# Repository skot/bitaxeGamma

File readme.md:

```
Open Source is Intrinsic to Bitcoin
```
# The bitaxeGamma
bitaxe is a fully open source Bitcoin ASIC miner aimed at decentralizing mining. bitaxeGamma is the 5th major revision of the bitaxe that now includes the BM1370 ASIC from the Antminer S21 Pro

## Goals
- **Easy**: Just plug it in and mine Bitcoin over WiFi. No external computer needed.
- **Practical**: low cost, low noise, low power, low maintenance. You can run this at home.
- **ASIC Power**: High efficiency and hashrate, based on the latest and greatest Application Specific Integrated Circuits.
- **Versatile**: Mine to any StratumV1 pool, Lottery mine, Solo mine, Or hack it to do whatever you want.
- **Bitcoin Ethos**: Fully open source, permissionless and decentralized to support the worldwide freedom money.

## ASIC
At the heart of the bitaxeGamma is a BM1370 Bitcoin mining ASIC from the Antminer S21 Pro from Bitmain. It's not open source.

- Bitmain claims the BM1370 has 15 J/TH efficiency. We can get pretty close to that with the BitaxeGamma
- The Antminer S21 Pro has a nominal hashrate of 234 TH/s. There are 3 hashboards with 65 chips each, for a total of 195 chips. The bitaxeGamma has a single one of these chips. That means _about_ 1.2 TH/s per bitaxeGamma. Initial testing looks good!
- The BM1370 is brand new and isn't available individually yet. The best place to get these chips is right out of a S21 Pro.
- The BM1370 has a different footprint and pinout from the BM1368, BM1366, BM1397 and BM1387 in previous bitaxe.

## Current Status
- BitaxeGamma 600 is working well and has been released!
- In addition to higher hashrate, the Gamma also uses more power. Please pay attemtion to hash frequency and voltage settings as it's much easier to overheat, especially when using the stock heatsink and fan.
- BM1370 firmware support has been added to [esp-miner](https://github.com/skot/esp-miner)
- Be sure to check the [HW issues](https://github.com/skot/bitaxe/issues) for known bugs, reworks and errata.
- This is an _advanced_ build! You can do it, but if you're not looking for a project, it might be best to buy one pre-assembled from one of the [many sellers](https://bitaxe.org/legit.html). Check [Skot's method](assembly.md) of hand assembling PCBs.

## PCB Hardware
This repo contains all of the design files for the PCB. [KiCAD](https://www.kicad.com) software is used. There is a BOM file for all of the components that get soldered to the PCB. 

- Order PCBs from your favorite PCB shop, like [JLCPCB](https://jlcpcb.com), [SeeedStudio](https://www.seeedstudio.com/fusion_pcb.html), or [PCBWay](https://www.pcbway.com)
    - Gerbers are in the `Manufacturing Files` dir. PCBs are 4-layer, 6mil trace/space and 0.3mm hole compatible. 1oz outer / 0.5oz inner layer thickness works well.
    - Make sure to order stencils too. These are the "paste" layers in the gerbers folder. one for top and one for bottom.
- All PCB parts except the ASIC are available from [DigiKey](https://www.digikey.com/en/products) and others. You can find Digikey part numbers on the DK tab of the BOM

## Extra Hardware
There are a few other hardware components that are needed for a complete bitaxe.

- **Heatsink**
	- [40x40mm heatsink and 5V fan](https://www.aliexpress.com/item/2251832861666365.html) from a random AliExpress seller. The fans are crap, but the heatsinks are good.  
- **Fan**
	- You **must** have active cooling on the bitaxe. The heatsink alone is not enough.
	- The Bitaxe has a connector for a 4pin, 5V PWM fan. 40mm square, 20mm thick fans work nicely with the suggested heatsink. Make sure to get a 5V fan! 12V spin, but slowly overheating your Bitaxe..
	- Upgrade your fan with the [Noctua NF-A4x10](https://noctua.at/en/nf-a4x10-5v-pwm) 5V 4-Pin fan for a much more pleasant experience.
- **Thermal compound**
	- Use a good quality thermal compound between the heatsink and ASIC. [Thermal Grizzly Kryonaut](https://www.amazon.com/Thermal-Grizzly-Kryonaut-Grease-Paste/dp/B011F7W3LU) has been known to work well.  
- **Display**
	- Supports 0.91" SSD1306-based I2C OLED Module. [Example Amazon seller](https://www.amazon.com/gp/product/B08ZY4YBHL). Make sure to get the male pins to interface with the Bitaxe PCB. 
- **Power Supply**
	- **5V DC Only!** Anything else will damage the Bitaxe. Be careful and double-check your power supply is 5V. Many other voltage power supplies use the same connector.
	- The power supply needs to supply in excess of 4A (20W) and not drop below 5V. Often times you have to use a power supply rated for 25-30W to get this!
 		- The [Meanwell GST60A05-P1J](https://www.digikey.com/en/products/detail/mean-well-usa-inc/GST60A05-P1J/7703709) at 30 Watts is the cadillac of 5V PSUs and is working well with the Gamma.  
	- The bitaxe uses a 5.5x2.1mm, center-positive barrel jack. 5.5x2.5mm plugs have been known to work.
- **Stand**
	- The PCB has corner mounting holes. You're going to want a stand to mount your Bitaxe. Many excellent 3D printed designs are available.

## Firmware
- The [ESP-Miner](https://github.com/skot/ESP-Miner) has initial support for the BM1370 ASIC. Improvements are ongoing.

### ESP32 Programming Requirements
- As of the bitaxeUltra, all ESP32 programming is done through a USB-C cable and connector on the bitaxe. See [ESP-Miner](https://github.com/skot/ESP-Miner) for more details.

## More Information
- Project page at [bitaxe.org](https://bitaxe.org)
- [Open Source Miners United](discord.gg/osmu) Discord chat
- [building.md](building.md) for PCB ordering tips
- [assembly.md](assembly.md) for assembly tips

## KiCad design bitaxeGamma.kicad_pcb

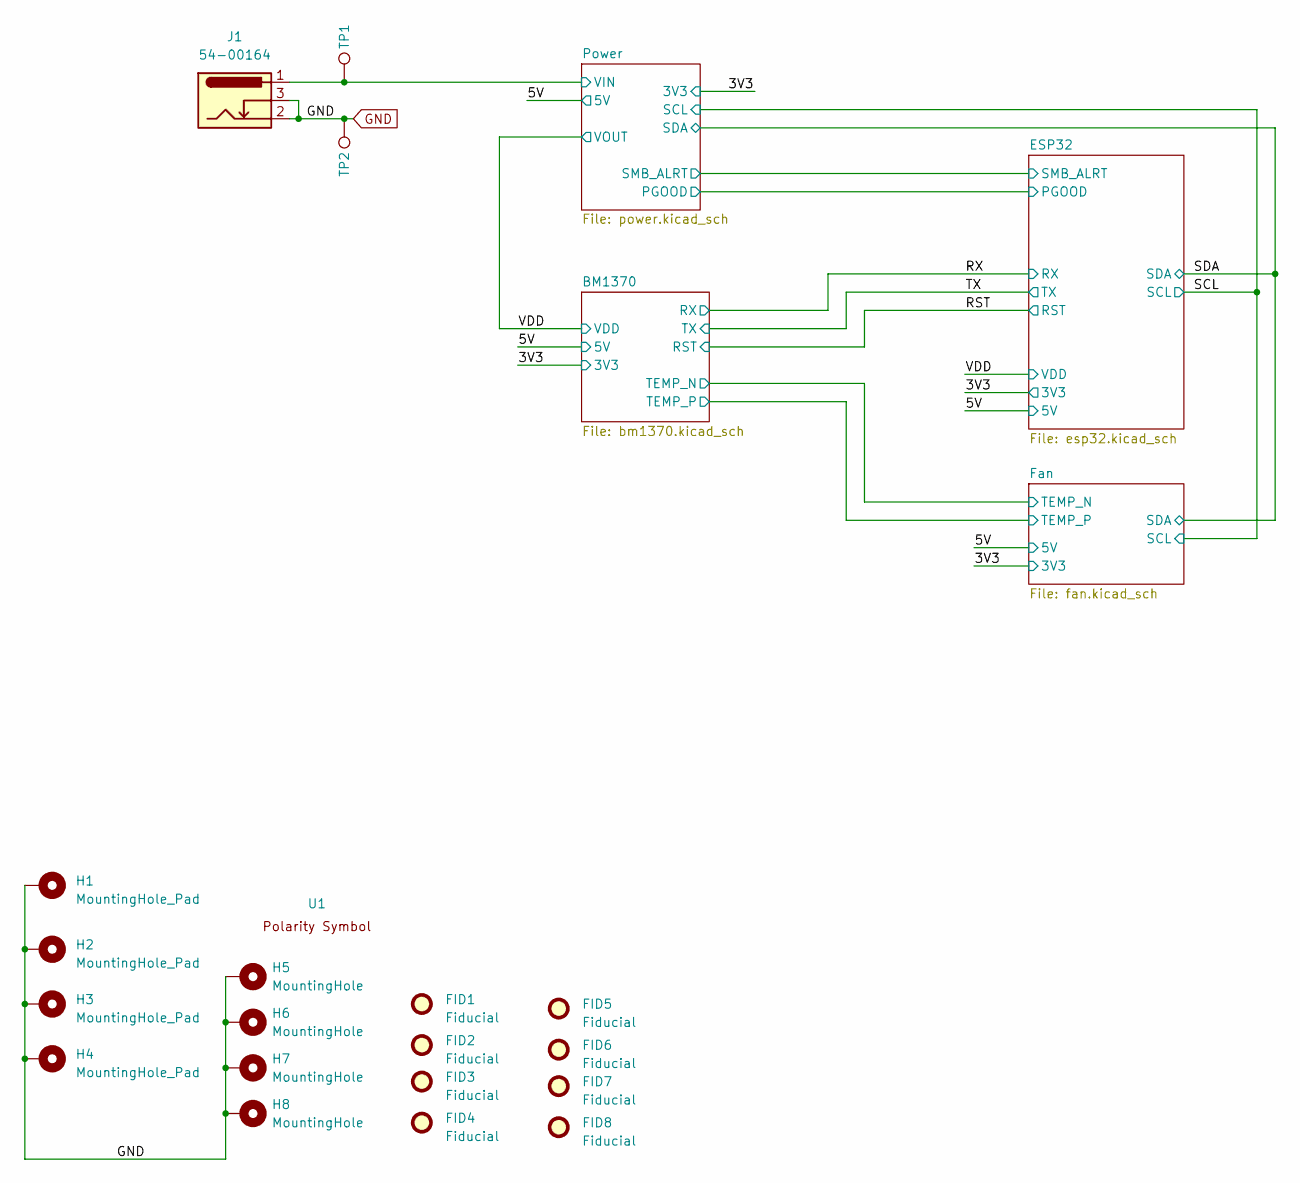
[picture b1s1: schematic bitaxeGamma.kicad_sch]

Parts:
FID1, FID2, FID3, FID4, FID5, FID6, FID7, FID8: Fiducial; Fiducial_1mm_Mask2mm
H1, H2, H3, H4: MountingHole_Pad; MountingHole_3mm_Pad_Via
H5, H6, H7, H8: MountingHole; MountingHole_3.2mm_M3_Pad
J1: 54-00164; TENSILITY_54-00164; PARTNO 54-00164; LCSC C431534
TP1, TP2: TestPoint; TestPoint_Pad_D1.5mm
U1: polarity

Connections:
/5V: J1.1, TP1.1; also elsewhere on the board

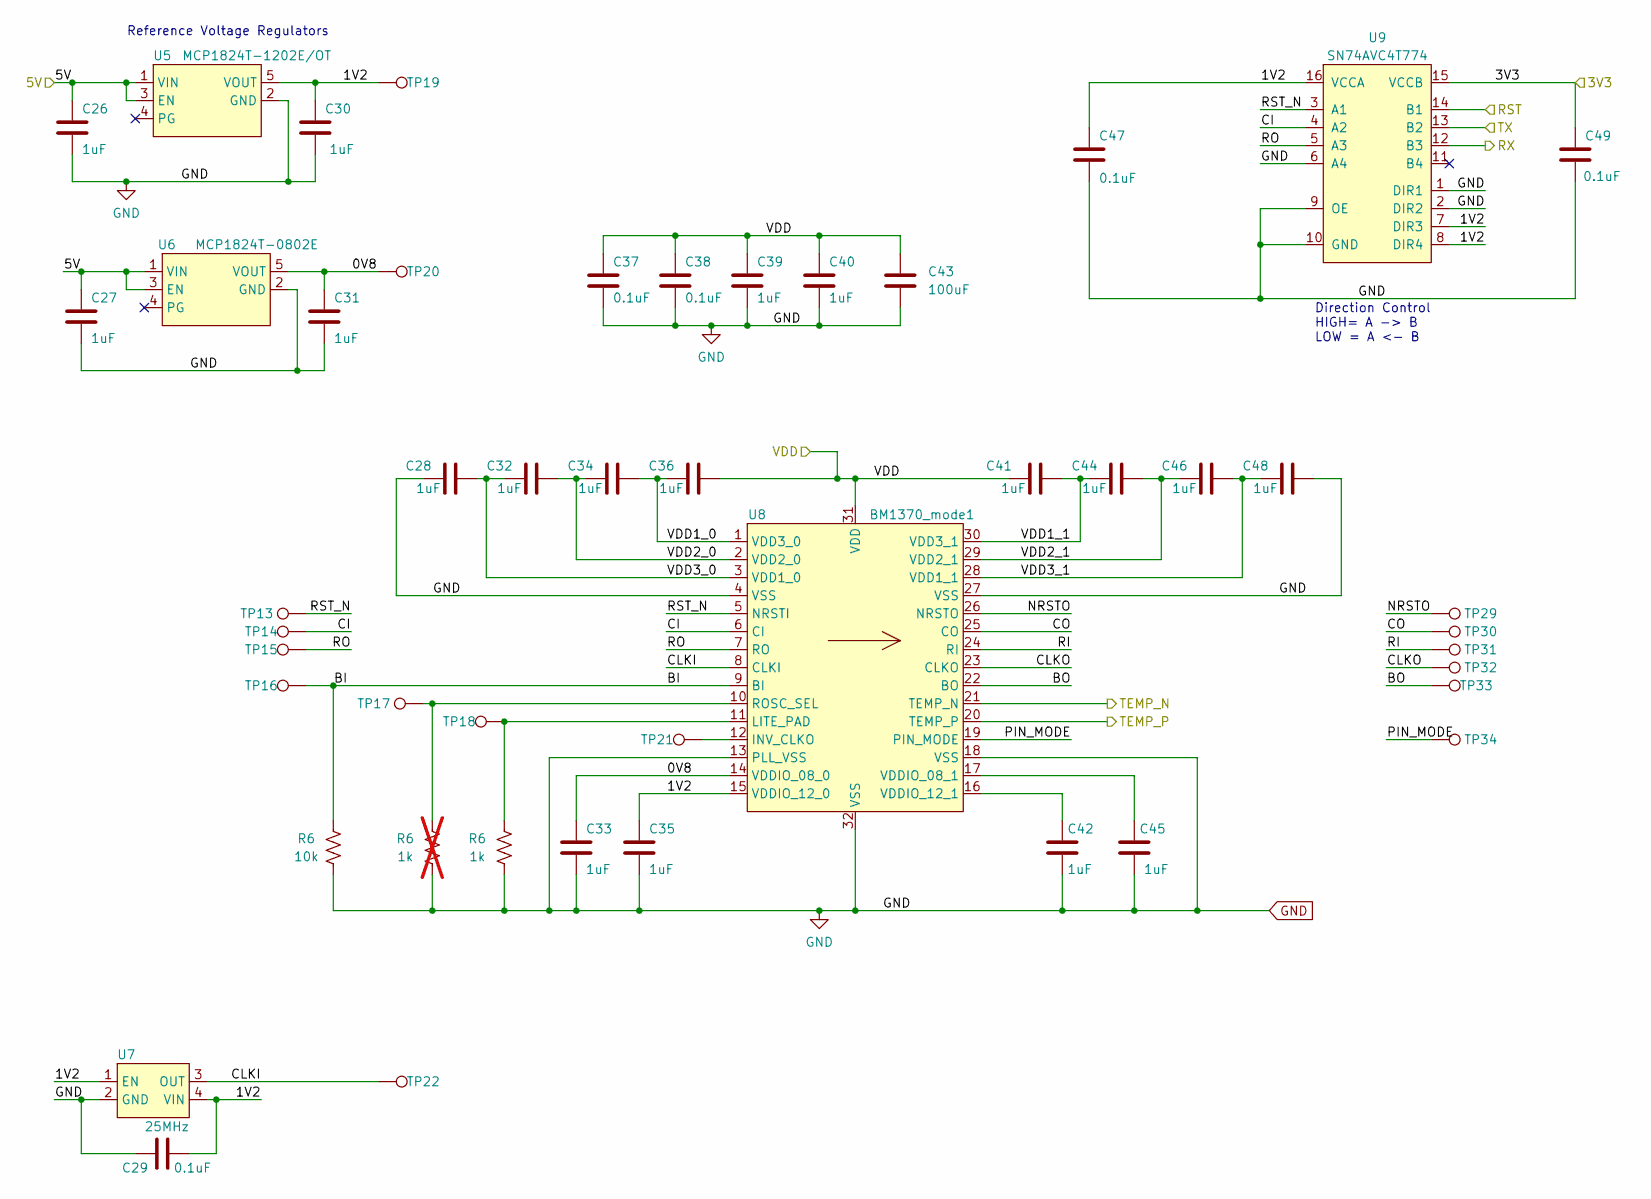
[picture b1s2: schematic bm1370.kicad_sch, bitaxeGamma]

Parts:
C26, C27, C28, C30, C31, C32, C33, C34, C35, C36, C39, C40, C41, C42, C44, C45, C46, C48: 1uF; C_0402_1005Metric; PARTNO EMK105BJ105MV-F
C29, C37, C38, C47, C49: 0.1uF; C_0402_1005Metric; PARTNO CL05A104KO5NNNC
C43: 100uF; C_1206_3216Metric; PARTNO CL31A107MQHNNNE
R6: 1k; R_0402_1005Metric; PARTNO RC0402FR-071KL; not fitted
TP13, TP14, TP15, TP16, TP17, TP18, TP19, TP20, TP21, TP22, TP29, TP30, TP31, TP32, TP33, TP34: TestPoint; TestPoint_Pad_D1.5mm
U5: MCP1824T-1202E/OT; SOT-23-5; PARTNO MCP1824T-1202E/OT
U6: MCP1824T-0802E; SOT-23-5; PARTNO MCP1824T-0802E/OT
U7: 25MHz; SMD3225-4P; PARTNO SX3M25.000E20F30THN; LCSC C5137262
U8: BM1370_mode1; BM1370
U9: SN74AVC4T774; TSSOP-16_4.4x5mm_P0.65mm; PARTNO SN74AVC4T774PWR

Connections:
/3V3: C49.1, U9.15 (VCCB); also elsewhere on the board
/5V: C26.1, C27.1, U5.1 (VIN), U5.3 (EN), U6.1 (VIN), U6.3 (EN); also elsewhere on the board
/BM1370/0V8: C31.1, C33.1, TP20.1, U6.5 (VOUT), U8.14 (VDDIO_08_0)
/BM1370/1V2: C29.2, C30.1, C35.1, C47.1, TP19.1, U5.5 (VOUT), U7.1 (EN), U7.4 (VIN), U8.15 (VDDIO_12_0), U9.7 (DIR3), U9.8 (DIR4), U9.16 (VCCA)
/BM1370/BO: TP33.1, U8.22 (BO)
/BM1370/CI: TP14.1, U8.6 (CI), U9.4 (A2)
/BM1370/CLKI: TP22.1, U7.3 (OUT), U8.8 (CLKI)
/BM1370/CLKO: TP32.1, U8.23 (CLKO)
/BM1370/CO: TP30.1, U8.25 (CO)
/BM1370/NRSTO: TP29.1, U8.26 (NRSTO)
/BM1370/PIN_MODE: TP34.1, U8.19 (PIN_MODE)
/BM1370/RI: TP31.1, U8.24 (RI)
/BM1370/RO: TP15.1, U8.7 (RO), U9.5 (A3)
/BM1370/RST_N: TP13.1, U8.5 (NRSTI), U9.3 (A1)
/BM1370/VDD1_0: C34.2, C36.1, U8.1 (VDD3_0)
/BM1370/VDD1_1: C41.2, C44.1, U8.30 (VDD3_1)
/BM1370/VDD2_0: C32.2, C34.1, U8.2 (VDD2_0)
/BM1370/VDD2_1: C44.2, C46.1, U8.29 (VDD2_1)
/BM1370/VDD3_0: C28.2, C32.1, U8.3 (VDD1_0)
/BM1370/VDD3_1: C46.2, C48.1, U8.28 (VDD1_1)
/Fan/TEMP_N: U8.21 (TEMP_N); also elsewhere on the board
/Fan/TEMP_P: U8.20 (TEMP_P); also elsewhere on the board
/RST: U9.14 (B1); also elsewhere on the board
/RX: U9.12 (B3); also elsewhere on the board
/TX: U9.13 (B2); also elsewhere on the board
/VDD: C36.2, C37.1, C38.1, C39.1, C40.1, C41.1, C43.1, U8.31 (VDD); also elsewhere on the board
unnamed: TP21.1, U8.12 (INV_CLKO)
unnamed: C45.1, U8.17 (VDDIO_08_1)
unnamed: C42.1, U8.16 (VDDIO_12_1)

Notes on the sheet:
Reference Voltage Regulators
Direction Control HIGH= A -> B LOW = A <- B

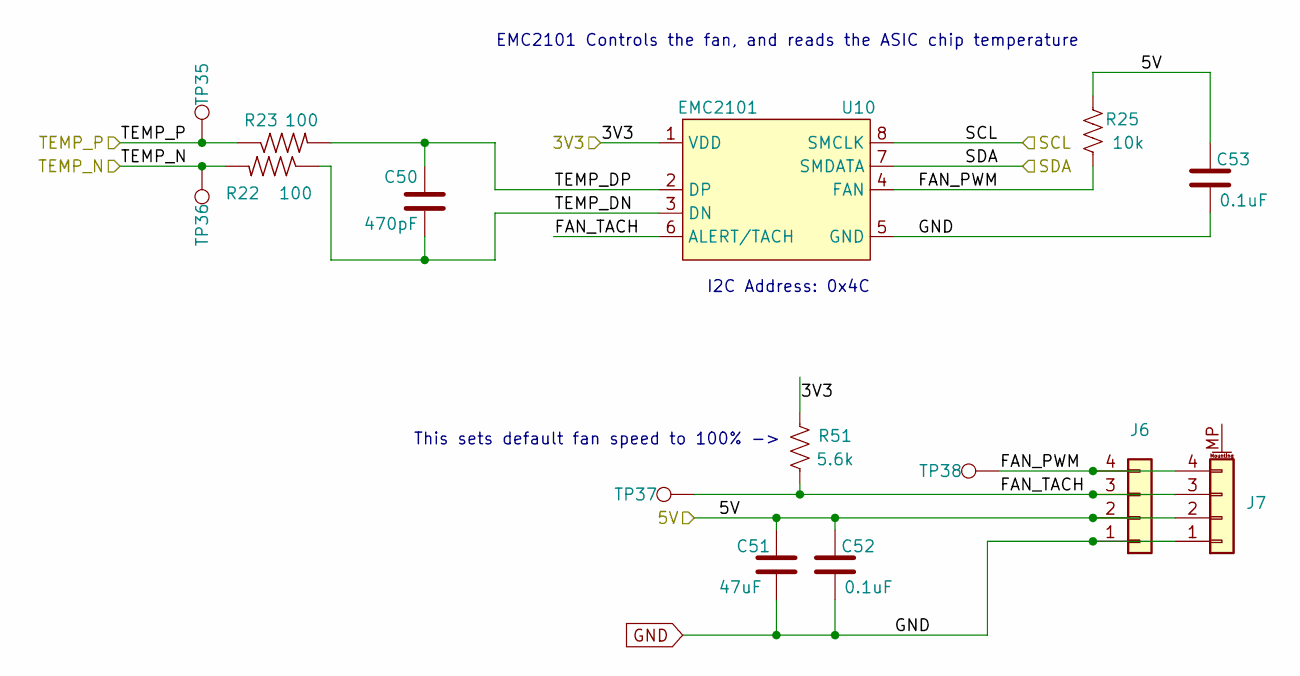
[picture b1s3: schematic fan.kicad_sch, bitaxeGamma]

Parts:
C50: 470pF; C_0402_1005Metric; PARTNO CL05B471KB5NNNC
C51: 47uF; C_1210_3225Metric; PARTNO CL32A476KOJNNNE
C52, C53: 0.1uF; C_0402_1005Metric; PARTNO CL05A104KO5NNNC
J6: Conn_01x04; 470531000; PARTNO 0470531000
J7: Conn_01x04; JST_SH_BM04B-SRSS-TB_1x04-1MP_P1.00mm_Vertical
R22, R23: 100; R_0402_1005Metric; PARTNO RC0402FR-07100RL
R25: 10k; R_0402_1005Metric; PARTNO RC0402JR-0710KL
R51: 5.6k; R_0402_1005Metric; PARTNO RC0402FR-135K6L
TP35, TP36, TP37, TP38: TestPoint; TestPoint_Pad_D1.5mm
U10: EMC2101; TSSOP-8_3x3mm_P0.65mm; PARTNO EMC2101-R-ACZL-TR

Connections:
/3V3: U10.1 (VDD); also elsewhere on the board
/5V: C51.1, C52.1, C53.1, J6.2, J7.2, R25.2; also elsewhere on the board
/Fan/FAN_PWM: J6.4, J7.4, R25.1, TP38.1, U10.4 (FAN)
/Fan/FAN_TACH: J6.3, J7.3, TP37.1, U10.6 (ALERT/TACH); also elsewhere on the board
/Fan/TEMP_DN: C50.2, R22.1, U10.3 (DN)
/Fan/TEMP_DP: C50.1, R23.2, U10.2 (DP)
/Fan/TEMP_N: R22.2, TP36.1; also elsewhere on the board
/Fan/TEMP_P: R23.1, TP35.1; also elsewhere on the board
/SCL: U10.8 (SMCLK); also elsewhere on the board
/SDA: U10.7 (SMDATA); also elsewhere on the board

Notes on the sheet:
EMC2101 Controls the fan, and reads the ASIC chip temperature
This sets default fan speed to 100% ->
I2C Address: 0x4C

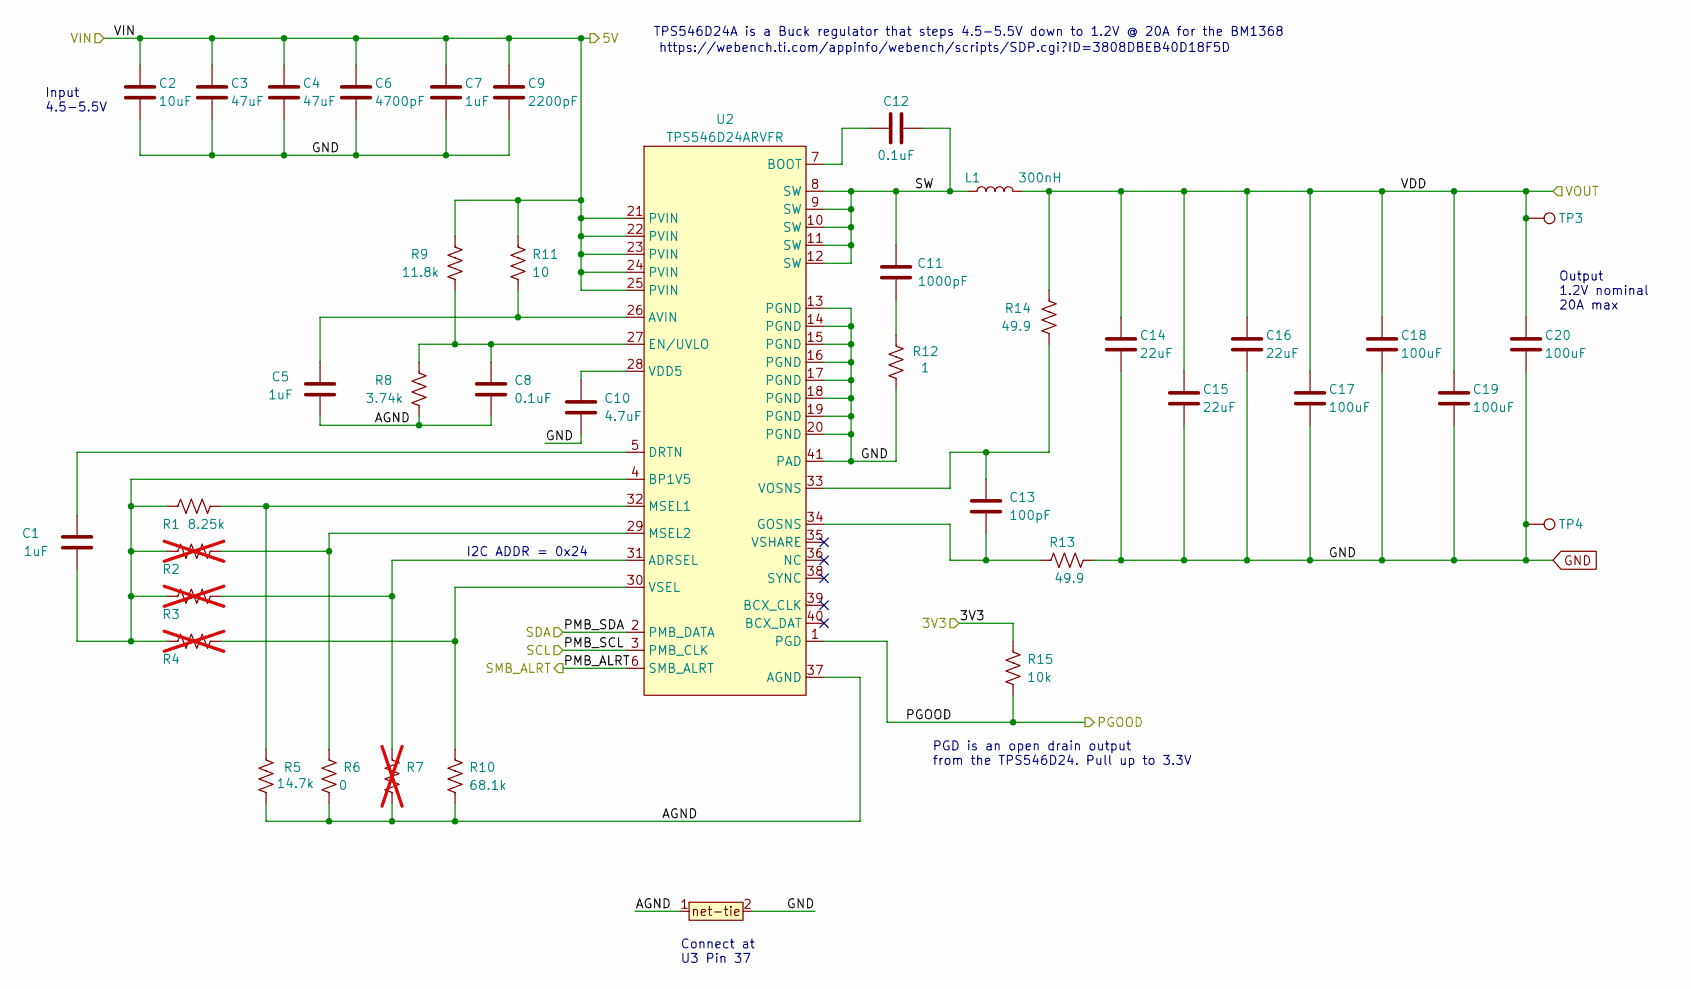
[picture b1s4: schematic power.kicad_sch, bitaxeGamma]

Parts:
C1, C5, C7: 1uF; C_0402_1005Metric; PARTNO EMK105BJ105MV-F
C2: 10uF; C_0805_2012Metric; PARTNO CL21A106KOQNNNE
C3, C4: 47uF; C_1210_3225Metric; PARTNO CL32A476KOJNNNE
C6: 4700pF; C_0402_1005Metric; PARTNO GRM155R71E472KA01D
C8, C12: 0.1uF; C_0402_1005Metric; PARTNO CL05A104KO5NNNC
C9: 2200pF; C_0402_1005Metric; PARTNO GRM155R61H222KA01D
C10: 4.7uF; C_0402_1005Metric; PARTNO GRM155R61A475MEAAD
C11: 1000pF; C_0805_2012Metric; PARTNO CC0805KRX7R9BB102
C13: 100pF; C_0402_1005Metric; PARTNO 885012005013
C14, C15, C16: 22uF; C_0805_2012Metric; PARTNO GRM21BR61A226ME44L
C17, C18, C19, C20: 100uF; C_1206_3216Metric; PARTNO CL31A107MQHNNNE
L1: 300nH; SLC1175-271MEC_COC; PARTNO SLC1175-301MEC; Mouser 994-SLC1175-271MEC
R1: 8.25k; R_0402_1005Metric; PARTNO RC0402FR-078K25L
R2, R3, R4, R7: R_0402_1005Metric; not fitted
R5: 14.7k; R_0402_1005Metric; PARTNO RC0402FR-0714K7L
R6: 0; R_0402_1005Metric; PARTNO RC0402JR-070RL
R8: 3.74k; R_0402_1005Metric; PARTNO RC0402FR-073K74L
R9: 11.8k; R_0402_1005Metric; PARTNO RC0402FR-0711K8L
R10: 68.1k; R_0402_1005Metric; PARTNO RC0402FR-0768K1L
R11: 10; R_0402_1005Metric; PARTNO RC0402FR-0710RL
R12: 1; R_1206_3216Metric; PARTNO CSR1206FT1R00
R13, R14: 49.9; R_0402_1005Metric; PARTNO RC0402FR-0749R9L
R15: 10k; R_0402_1005Metric; PARTNO RC0402JR-0710KL
T1: net-tie; NetTie-0.25mm; PARTNO 2R5TPE220MAFB
TP3, TP4: TestPoint; TestPoint_Pad_D1.5mm
U2: TPS546D24ARVFR; LQFN40-CLIP; PARTNO TPS546D24ARVFR

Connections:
/3V3: R15.2; also elsewhere on the board
/5V: C2.1, C3.1, C4.1, C6.1, C7.1, C9.1, R9.1, R11.1, U2.21 (PVIN), U2.22 (PVIN), U2.23 (PVIN), U2.24 (PVIN), U2.25 (PVIN); also elsewhere on the board
/Power/PGOOD: R15.1, U2.1 (PGD); also elsewhere on the board
/Power/PMB_ALRT: U2.6 (SMB_ALRT); also elsewhere on the board
/Power/SW: C11.2, C12.2, L1.1, U2.8 (SW), U2.9 (SW), U2.10 (SW), U2.11 (SW), U2.12 (SW)
/SCL: U2.3 (PMB_CLK); also elsewhere on the board
/SDA: U2.2 (PMB_DATA); also elsewhere on the board
/VDD: C14.1, C15.1, C16.1, C17.1, C18.1, C19.1, C20.1, L1.2, R14.1, TP3.1; also elsewhere on the board
unnamed: C11.1, R12.2
unnamed: R3.2, R7.1, U2.31 (ADRSEL)
unnamed: C5.2, R11.2, U2.26 (AVIN)
unnamed: C12.1, U2.7 (BOOT)
unnamed: C1.2, R1.1, R2.1, R3.1, R4.1, U2.4 (BP1V5)
unnamed: C1.1, U2.5 (DRTN)
unnamed: C8.1, R8.1, R9.2, U2.27 (EN/UVLO)
unnamed: C13.2, R13.1, U2.34 (GOSNS)
unnamed: R1.2, R5.2, U2.32 (MSEL1)
unnamed: C10.1, U2.28 (VDD5)
unnamed: C13.1, R14.2, U2.33 (VOSNS)
unnamed: R4.2, R10.1, U2.30 (VSEL)

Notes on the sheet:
TPS546D24A is a Buck regulator that steps 4.5-5.5V down to 1.2V @ 20A for the BM1368
https://webench.ti.com/appinfo/webench/scripts/SDP.cgi?ID=3808DBEB40D18F5D
Input 4.5-5.5V
PGD is an open drain output from the TPS546D24. Pull up to 3.3V
I2C ADDR = 0x24
Output 1.2V nominal 20A max
Connect at U3 Pin 37

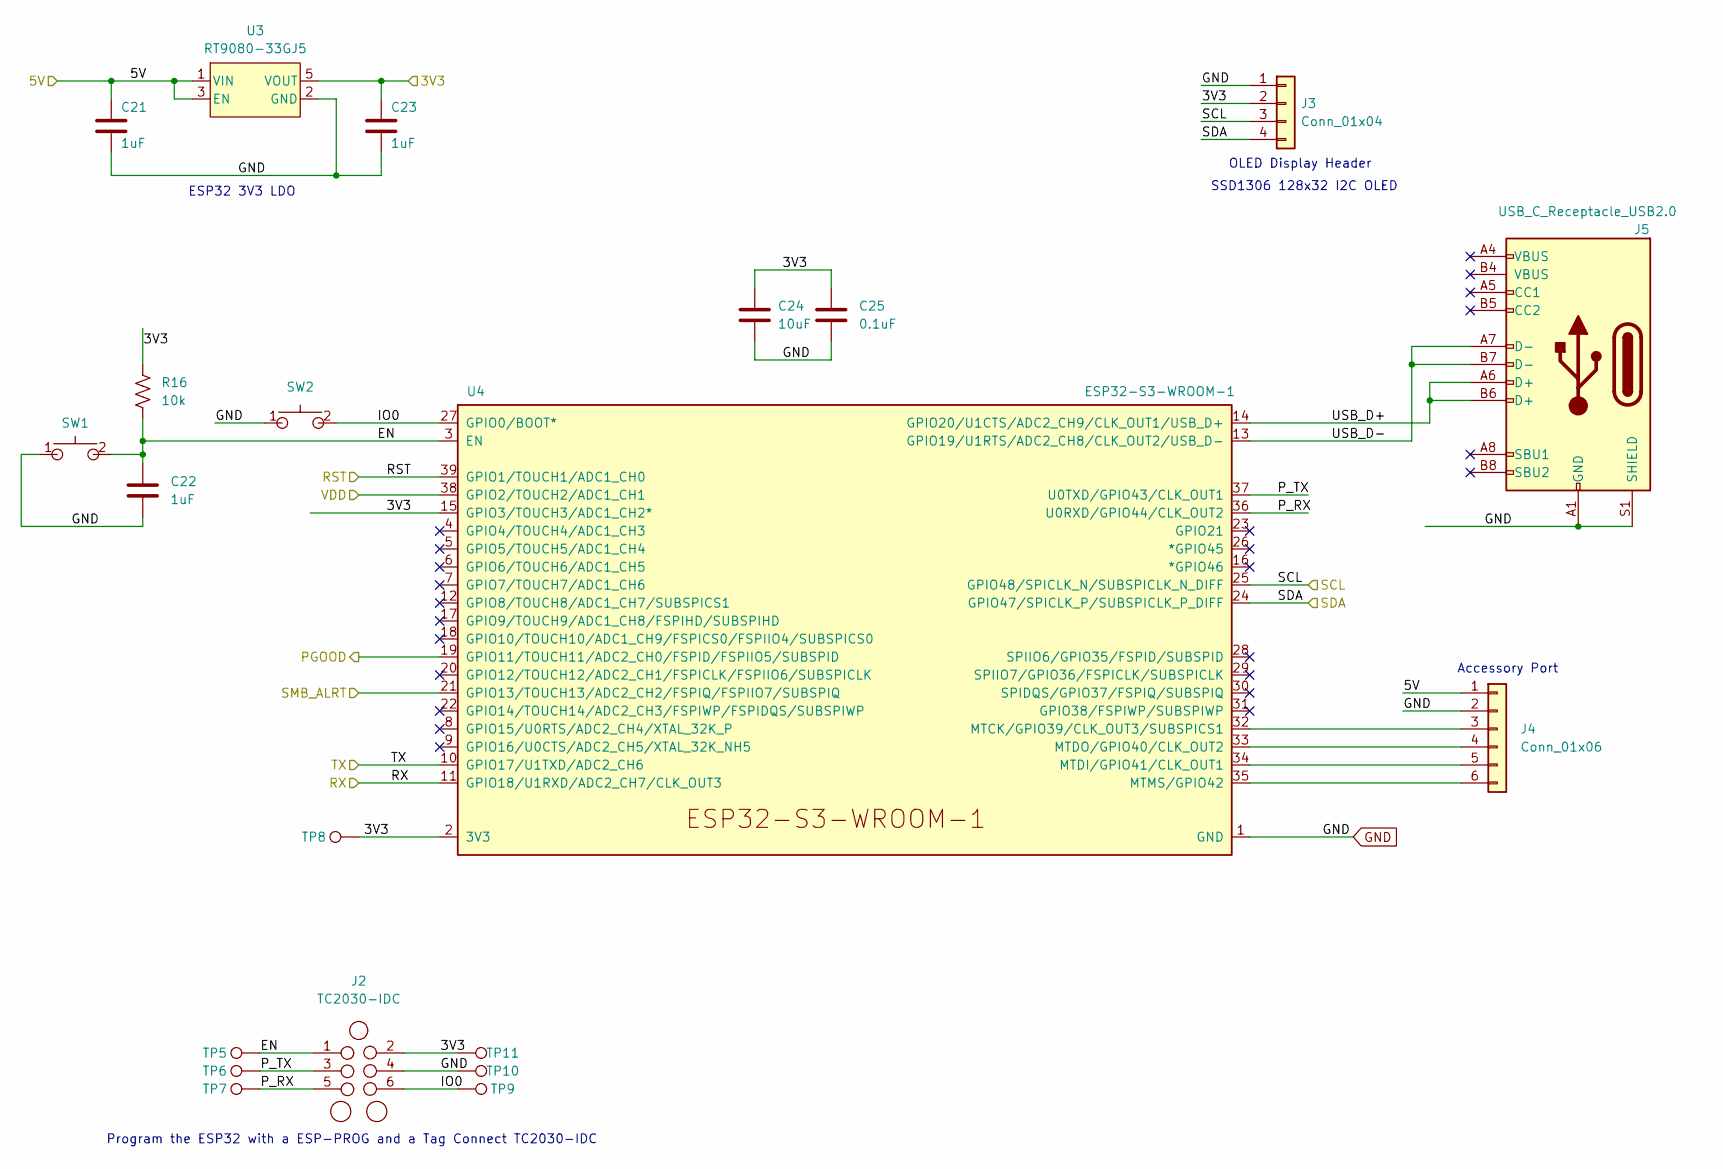
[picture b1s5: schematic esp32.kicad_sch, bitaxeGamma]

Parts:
C21, C22, C23: 1uF; C_0402_1005Metric; PARTNO EMK105BJ105MV-F
C24: 10uF; C_0805_2012Metric; PARTNO CL21A106KOQNNNE
C25: 0.1uF; C_0402_1005Metric; PARTNO CL05A104KO5NNNC
J2: TC2030-IDC; Tag-Connect_TC2030-IDC-NL_2x03_P1.27mm_Vertical
J3: Conn_01x04; PinHeader_1x04_P2.54mm_Vertical_shifted; PARTNO NPTC041KFXC-RC
J4: Conn_01x06; PinHeader_1x06_P2.54mm_Vertical
J5: USB_C_Receptacle_USB2.0; USB_C_Receptacle_GCT_USB4105-xx-A; PARTNO USB4105-GF-A
R16: 10k; R_0402_1005Metric; PARTNO RC0402JR-0710KL
SW1, SW2: GT-TC029B-H025-L1N; SW_CS1213AGF260_CRS; PARTNO CS1213AGF260
TP5, TP6, TP7, TP8, TP9, TP10, TP11: TestPoint; TestPoint_Pad_D1.5mm
U3: RT9080-33GJ5; PARTNO RT9080-33GJ5
U4: ESP32-S3-WROOM-1; PARTNO ESP32-S3-WROOM-1-N16R8

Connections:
/3V3: C23.1, C24.1, C25.1, J2.2, J3.2, R16.1, TP8.1, TP11.1, U3.5 (VOUT), U4.2 (3V3), U4.15 (GPIO3/TOUCH3/ADC1_CH2*); also elsewhere on the board
/5V: C21.1, J4.1, U3.1 (VIN), U3.3 (EN); also elsewhere on the board
/ESP32/EN: C22.1, J2.1, R16.2, SW1.2, TP5.1, U4.3 (EN)
/ESP32/IO0: J2.6, SW2.2, TP9.1, U4.27 (GPIO0/BOOT*)
/ESP32/P_RX: J2.5, TP7.1, U4.36 (U0RXD/GPIO44/CLK_OUT2)
/ESP32/P_TX: J2.3, TP6.1, U4.37 (U0TXD/GPIO43/CLK_OUT1)
/ESP32/USB_D+: J5.A6 (D+), J5.B6 (D+), U4.14 (GPIO20/U1CTS/ADC2_CH9/CLK_OUT1/USB_D+)
/ESP32/USB_D-: J5.A7 (D-), J5.B7 (D-), U4.13 (GPIO19/U1RTS/ADC2_CH8/CLK_OUT2/USB_D-)
/Power/PGOOD: U4.19 (GPIO11/TOUCH11/ADC2_CH0/FSPID/FSPIIO5/S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); also elsewhere on the board
/Power/PMB_ALRT: U4.21 (GPIO13/TOUCH13/ADC2_CH2/FSPIQ/FSPIIO7/S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); also elsewhere on the board
/RST: U4.39 (GPIO1/TOUCH1/ADC1_CH0); also elsewhere on the board
/RX: U4.11 (GPIO18/U1RXD/ADC2_CH7/CLK_OUT3); also elsewhere on the board
/SCL: J3.3, U4.25 (GPIO48/SPICLK_N/SUBSPICLK_N_DIFF); also elsewhere on the board
/SDA: J3.4, U4.24 (GPIO47/SPICLK_P/SUBSPICLK_P_DIFF); also elsewhere on the board
/TX: U4.10 (GPIO17/U1TXD/ADC2_CH6); also elsewhere on the board
/VDD: U4.38 (GPIO2/TOUCH2/ADC1_CH1); also elsewhere on the board
unnamed: J4.3, U4.32 (MTCK/GPIO39/CLK_OUT3/SUBSPICS1)
unnamed: J4.4, U4.33 (MTDO/GPIO40/CLK_OUT2)
unnamed: J4.5, U4.34 (MTDI/GPIO41/CLK_OUT1)
unnamed: J4.6, U4.35 (MTMS/GPIO42)

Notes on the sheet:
Accessory Port
ESP32 3V3 LDO
Program the ESP32 with a ESP-PROG and a Tag Connect TC2030-IDC
SSD1306 128x32 I2C OLED
OLED Display Header

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
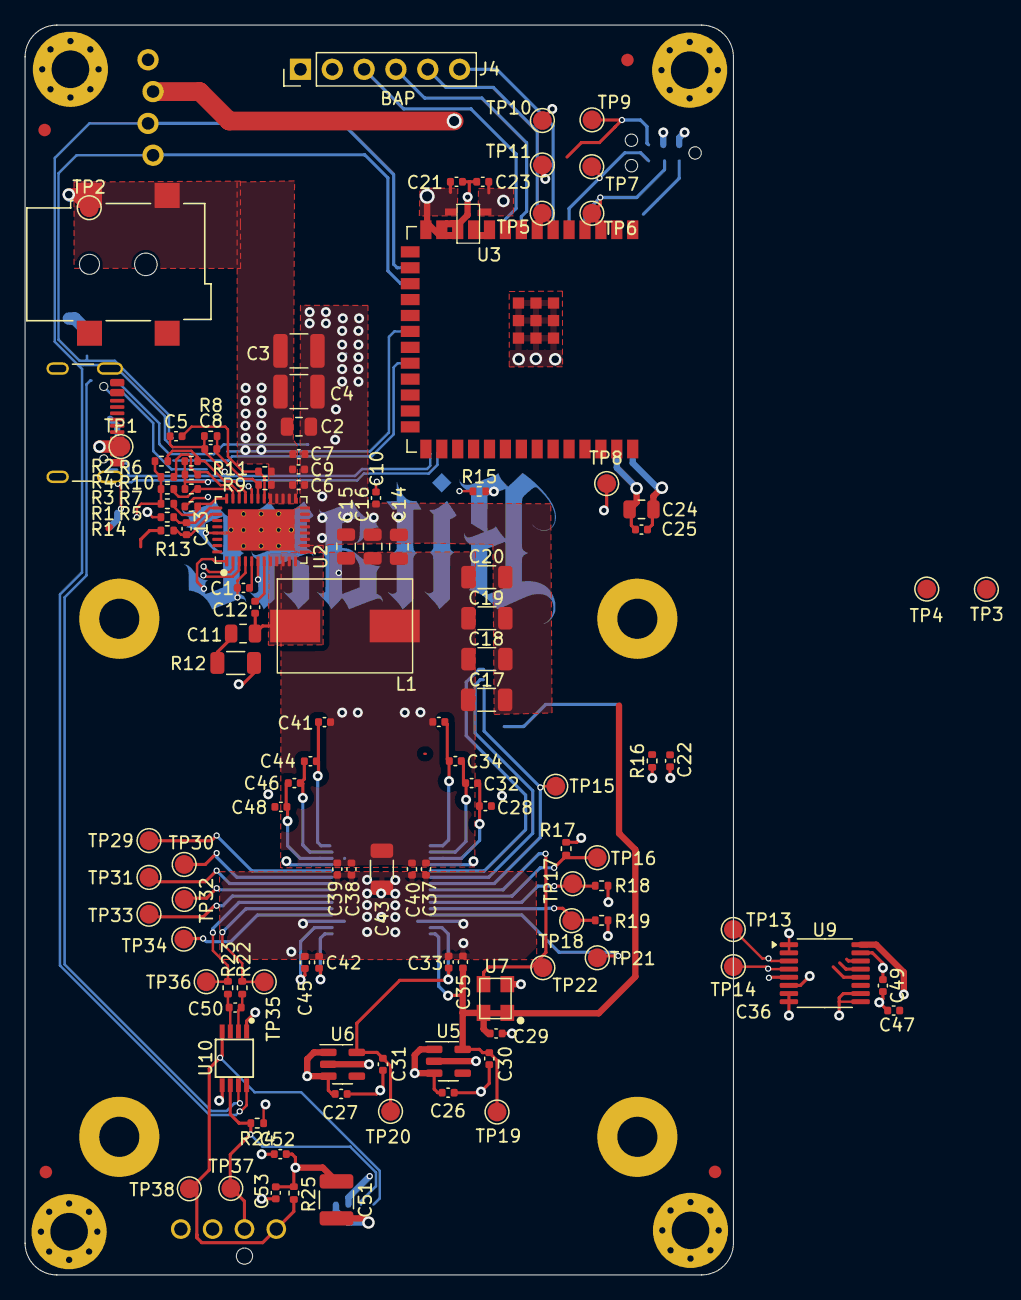
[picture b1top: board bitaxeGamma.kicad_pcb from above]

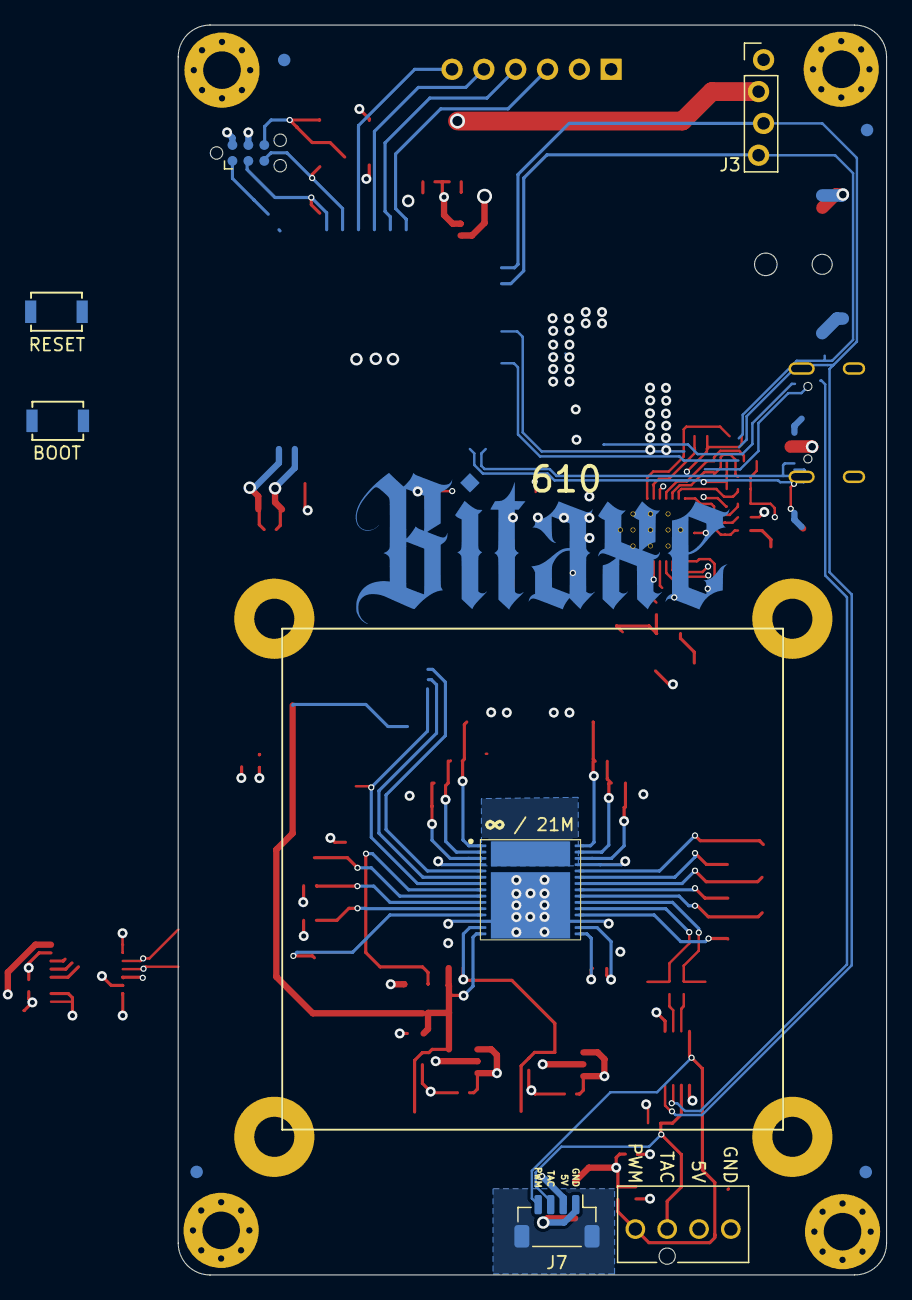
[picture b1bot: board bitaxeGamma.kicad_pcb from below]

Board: 4 copper layers, 56.5 x 99.8 mm, 144 parts (12 on the bottom side), 66 nets.

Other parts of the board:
R17: 10k; R_0402_1005Metric
R18, R19: 1k; R_0402_1005Metric
R24: 5.6k; R_0402_1005Metric

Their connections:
/3V3: R24.2; also elsewhere on the board
/Fan/FAN_TACH: R24.1; also elsewhere on the board

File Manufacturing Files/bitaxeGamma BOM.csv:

Qty,Reference,Value,Footprint,DK,PARTNO,DNP
1,C6,4700pF,Capacitor_SMD:C_0402_1005Metric,490-1309-1-ND,GRM155R71E472KA01D,
1,C9,2200pF,Capacitor_SMD:C_0402_1005Metric,490-8257-1-ND,GRM155R61H222KA01D,
1,C10,4.7uF,Capacitor_SMD:C_0402_1005Metric,490-14306-1-ND,GRM155R61A475MEAAD,
1,C11,1000pF,Capacitor_SMD:C_0805_2012Metric,311-1127-1-ND,CC0805KRX7R9BB102,
1,C13,100pF,Capacitor_SMD:C_0402_1005Metric,732-7431-1-ND,8.85012E+11,
1,C50,470pF,Capacitor_SMD:C_0402_1005Metric,1276-1566-1-ND,CL05B471KB5NNNC,
24,C1 C5 C7 C21 C22 C23 C26 C27 C28 C30 C31 C32 C33 C34 C35 C36 C39 C40 C41 C42 C44 C45 C46 C48,1uF,Capacitor_SMD:C_0402_1005Metric,587-5514-1-ND,EMK105BJ105MV-F,
3,C14 C15 C16,22uF,Capacitor_SMD:C_0805_2012Metric,490-10746-1-ND,GRM21BR61A226ME44L,
5,C17 C18 C19 C20 C43,100uF,Capacitor_SMD:C_1206_3216Metric,1276-1782-1-ND,CL31A107MQHNNNE,
2,C2 C24,10uF,Capacitor_SMD:C_0805_2012Metric,1276-1096-1-ND,CL21A106KOQNNNE,
3,C3 C4 C51,47uF,Capacitor_SMD:C_1210_3225Metric,1276-3376-1-ND,CL32A476KOJNNNE,
10,C8 C12 C25 C29 C37 C38 C47 C49 C52 C53,0.1uF,Capacitor_SMD:C_0402_1005Metric,1276-1234-1-ND,CL05A104KO5NNNC,
1,J1,54-00164,bitaxe:TENSILITY_54-00164,839-54-00164CT-ND,54-00164,
1,J5,USB_C_Receptacle_USB2.0,bitaxe:USB_C_Receptacle_GCT_USB4105-xx-A,2073-USB4105-GF-ACT-ND,USB4105-GF-A,
1,J6,Conn_01x04,bitaxe:470531000,WM4330-ND,470531000,
1,L1,300nH,bitaxe:SLC1175-271MEC_COC,,SLC1175-301MEC,
1,R1,8.25k,Resistor_SMD:R_0402_1005Metric,311-8.25KLRCT-ND,RC0402FR-078K25L,
1,R5,14.7k,Resistor_SMD:R_0402_1005Metric,YAG2984CT-ND,RC0402FR-0714K7L,
1,R6,0,Resistor_SMD:R_0402_1005Metric,311-0.0JRCT-ND,RC0402JR-070RL,
1,R8,3.74k,Resistor_SMD:R_0402_1005Metric,311-3.74KLRCT-ND,RC0402FR-073K74L,
1,R9,11.8k,Resistor_SMD:R_0402_1005Metric,YAG2958CT-ND,RC0402FR-0711K8L,
1,R10,68.1k,Resistor_SMD:R_0402_1005Metric,YAG3213CT-ND,RC0402FR-0768K1L,
1,R11,10,Resistor_SMD:R_0402_1005Metric,311-10.0LRCT-ND,RC0402FR-0710RL,
1,R12,1,Resistor_SMD:R_1206_3216Metric,CSR1206FT1R00CT-ND,CSR1206FT1R00,
1,R21,20k,Resistor_SMD:R_0402_1005Metric,311-20.0KLRCT-ND,RC0402FR-0720KL,
1,R24,5.6k,Resistor_SMD:R_0402_1005Metric,13-RC0402FR-135K6LCT-ND,RC0402FR-135K6L,
2,R13 R14,49.9,Resistor_SMD:R_0402_1005Metric,311-49.9LRCT-ND,RC0402FR-0749R9L,
4,R15 R16 R17 R25,10k,Resistor_SMD:R_0402_1005Metric,311-10KJRCT-ND,RC0402JR-0710KL,
2,R19,1k,Resistor_SMD:R_0402_1005Metric,311-1.00KLRCT-ND,RC0402FR-071KL,
2,R22 R23,100,Resistor_SMD:R_0402_1005Metric,311-100LRCT-ND,RC0402FR-07100RL,
2,SW1 SW2,GT-TC029B-H025-L1N,bitaxe:SW_CS1213AGF260_CRS,2449-CS1213AGF260CT-ND,CS1213AGF260,
1,U2,TPS546D24ARVFR,bitaxe:LQFN40-CLIP,296-TPS546D24ARVFRCT-ND,TPS546D24ARVFR,
1,U3,RT9080-33GJ5,bitaxe:RT9080-33GJ5,1028-1509-1-ND,RT9080-33GJ5,
1,U4,ESP32-S3-WROOM-1,bitaxe:ESP32-S3-WROOM-1,1965-ESP32-S3-WROOM-1-N16R8CT-ND,ESP32-S3-WROOM-1-N16R8,
1,U5,MCP1824T-1202E/OT,Package_TO_SOT_SMD:SOT-23-5,MCP1824T-1202E/OTCT-ND,MCP1824T-1202E/OT,
1,U6,MCP1824T-0802E,Package_TO_SOT_SMD:SOT-23-5,MCP1824T-0802E/OTCT-ND,MCP1824T-0802E/OT,
1,U7,25MHz,bitaxe:SMD3225-4P,O-25-0-JO32-B-1V3-1-T1-LF,SX3M25.000E20F30THN,
1,U8,BM1370_mode1,bitaxe:BM1370,,,
1,U9,SN74AVC4T774,Package_SO:TSSOP-16_4.4x5mm_P0.65mm,296-24739-1-ND,SN74AVC4T774PWR,
1,U10,EMC2101,Package_SO:TSSOP-8_3x3mm_P0.65mm,EMC2101-R-ACZL-CT-ND,EMC2101-R-ACZL-TR,

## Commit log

2024-07-02 switching to gamma/600 naming
2024-07-03 added BM1370 footprint
2024-07-03 added gerbers, BOM, updated readme and render
2024-07-03 small readme update
2024-07-03 BOM update
2024-07-05 fix oscillator name
2024-08-16 bump version to 600
2024-08-16 readme update
2024-08-19 Update readme.md with correct S21 Pro stated efficiency
2024-08-19 remove old photos. add real gamma pic to readme.
2024-08-19 add bitaxeLegit List link to readme
2024-08-19 fix typo on readme
2024-08-19 add schematic pdf
2024-08-20 JST fan connector
2024-08-20 better fan routing
2024-08-21 fan routing and MP anchor
2024-09-16 Fix: 100pF capacitor product number on BOM
2024-09-19 remove J3 from BOM for #2
2024-09-20 update readme with display male pins requirement
2024-09-20 update readme with Kryonaut thermal paste recommendation.
2024-09-26 remove old gerbers
2024-09-26 bump version to 602. remove R21 and fix for #6
2024-09-26 Revert "bump version to 602. remove R21 and fix for #6"
    This reverts commit 8bd74c865f9910776743c8aa45b35babe35214af.
2024-10-07 removed R18 and fixed U7 cursed part number
    R18 is DNP, so removed it;
    U7 part number was put in DNP column because of extra comma
2024-10-07 fixed U7 DigiKey part number
    And fixed DK part number (forgot the O-25 prefix)
    O-25-0-JO32-B-1V3-1-T1-LF
2024-10-10 fix typos in BOM. Improve BOM generator output
2024-11-02 barrel plug footprint, inductor footprint, asic footprint, gnd fill
2024-11-12 fix zones...
2024-11-14 Angel Wish License
2024-11-17 beefing up ASIC VDD width
2024-11-26 added 601 gerbers, BOM and iBOM
2024-11-26 update schematic PDF
2024-12-01 TPS546 is SMD
2024-12-02 fix no power to 5v inner trace and 3v3 emc2101
2024-12-14 BitAxe Gamma Heatsink Hole DXF
    This is the hole pattern for the existing Gamma heatsink+Fan Assembly
2024-12-14 repair the heatsink mounting hole parts and nudge them back into a symmetrical pattern
2024-12-14 switched heatsink mounting holes to all plated M3 (3.2mm) holes, on 41.35mm square pattern. removed thermals from all mounting holes
2024-12-14 starting to rearrange things. renamed to 610
2024-12-26 added github ci workflow
2024-12-27 update license to CERN-OHL-S
